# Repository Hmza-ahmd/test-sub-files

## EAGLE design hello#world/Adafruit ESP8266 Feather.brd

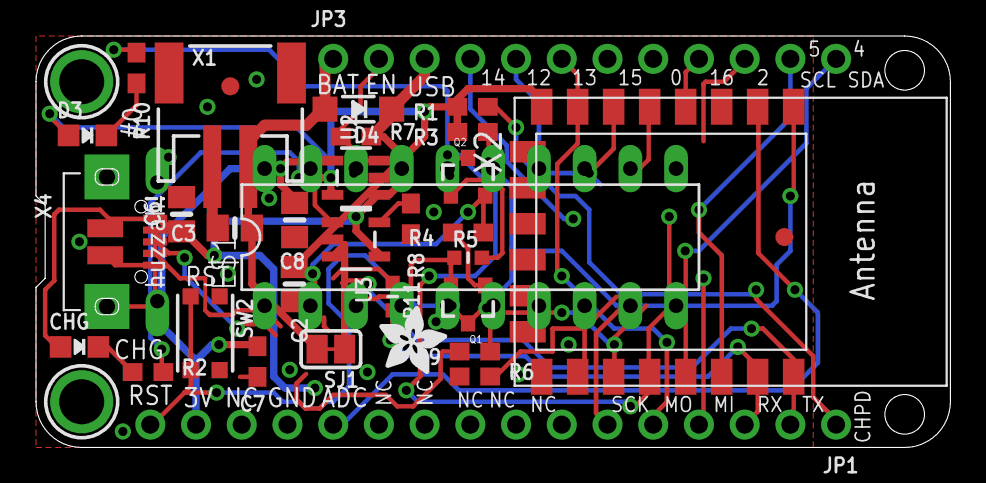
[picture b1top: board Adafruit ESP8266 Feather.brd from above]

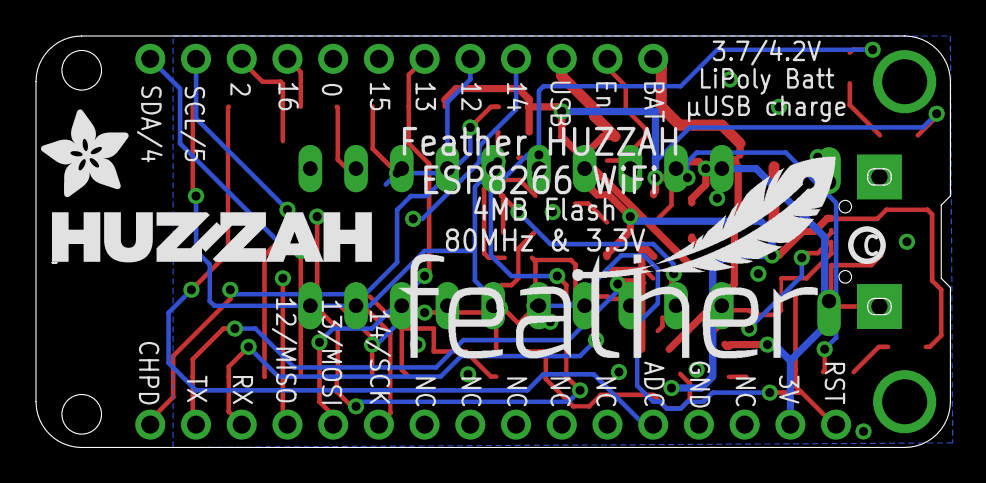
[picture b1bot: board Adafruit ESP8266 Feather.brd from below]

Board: 2 copper layers, 50.8 x 22.9 mm, 40 parts (4 on the bottom side), 27 nets.

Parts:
C2: 10uF; 0805-NO
C3, C6, C8: 10µF; 0805-NO
C7: 1uF; 0603-NO
CHG: ORANGE; CHIPLED_0805_NOOUTLINE
D3: RED; CHIPLED_0805_NOOUTLINE
D4: MBR120; SOD-123
E$1: DIL20
JP1: 1X16_ROUND
JP3: 1X12_ROUND
Q1, Q2: mmbt2222; SOT23-3
R1, R3, R4, R7, R9: 10K; 0603-NO
R2, R10: 1K; 0603-NO
R5: 10K; _0603MP
R6: 4.7K; 0603-NO
R8: 10K\; 0603-NO
R11: 1K; _0603MP
SJ1: SOLDERJUMPER_CLOSEDWIRE
SW2: KMR2; BTN_KMR2_4.6X2.8
U2: SPX3819; SOT23-5
U3: MCP73831T-2ACI/OT; SOT23-5
U$7: ADAFRUIT_5MM
U$9: FEATHERLOGO
U$13: PCBFEAT-REV-040
U$15: ADAFRUIT_3.5MM
U$23: HUZZAHLOGO
U$31, U$32: MOUNTINGHOLE2.5; MOUNTINGHOLE_2.5_PLATED
U$34, U$35: FIDUCIAL""; FIDUCIAL_1MM
X1: JSTPH; JSTPH2
X2: ESP-12; ESP-12E
X4: 20329; 4UCONN_20329_V2

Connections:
3.3V: C2.1, C7.1, C8.1, D3.A, JP1.15, R1.2, R3.2, R9.2, U2.5, X2.8
ADC: JP1.12, X2.2
CH_PD: JP1.1, R1.1
DTR: Q2.2, R4.1
EN: JP3.2, R7.1, U2.3
GND: C2.2, C3.2, C6.2, C7.2, C8.2, JP1.13, R6.1, R8.2, SW2.A, SW2.A', U2.2, U3.2, X1.1, X2.9, X4.BASE@1, X4.BASE@2, X4.GND, X4.SPRT@1, X4.SPRT@2, X4.SPRT@3, X4.SPRT@4
GPIO0: Q2.3, R10.1, X2.12
GPIO2: R9.1, X2.11
GPIO4/SDA: JP3.12, X2.13
GPIO5/SCL: JP3.11, X2.14
GPIO12/MISO: JP3.5, X2.6
GPIO13/MOSI: JP1.5, JP3.6, X2.7
GPIO15: R6.2, X2.10
GPIO16: JP3.9, X2.4
unnamed: CHG.C, R2.1
unnamed: R2.2, U3.1
unnamed: R8.1, U3.5
unnamed: D3.C, R10.2
unnamed: SJ1.1, U3.3
unnamed: Q1.1, R4.2
unnamed: Q2.1, R5.2
RESET: JP1.16, Q1.3, R3.1, SW2.B, SW2.B', X2.1
RTS: Q1.2, R5.1
RXD: JP1.3, R11.2, X2.15
TXD: JP1.2, X2.16
VBAT: C3.1, D4.A, JP3.1, SJ1.2, X1.2
VBUS: C6.1, CHG.A, D4.C, JP3.3, R7.2, U2.1, U3.4, X4.VBUS

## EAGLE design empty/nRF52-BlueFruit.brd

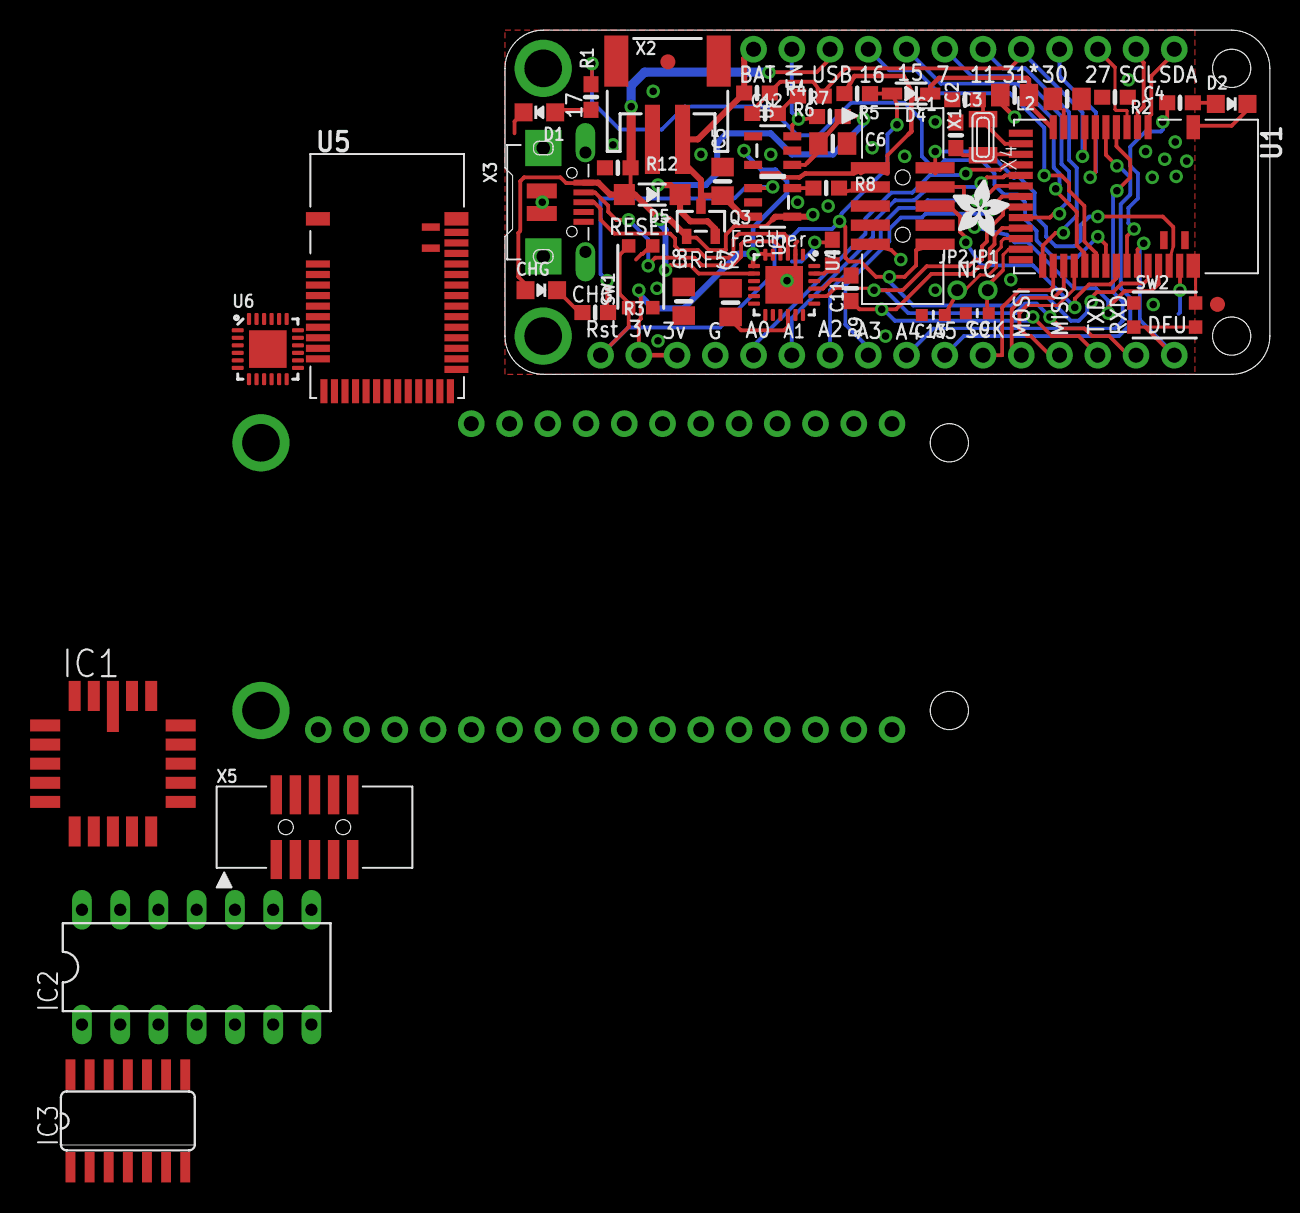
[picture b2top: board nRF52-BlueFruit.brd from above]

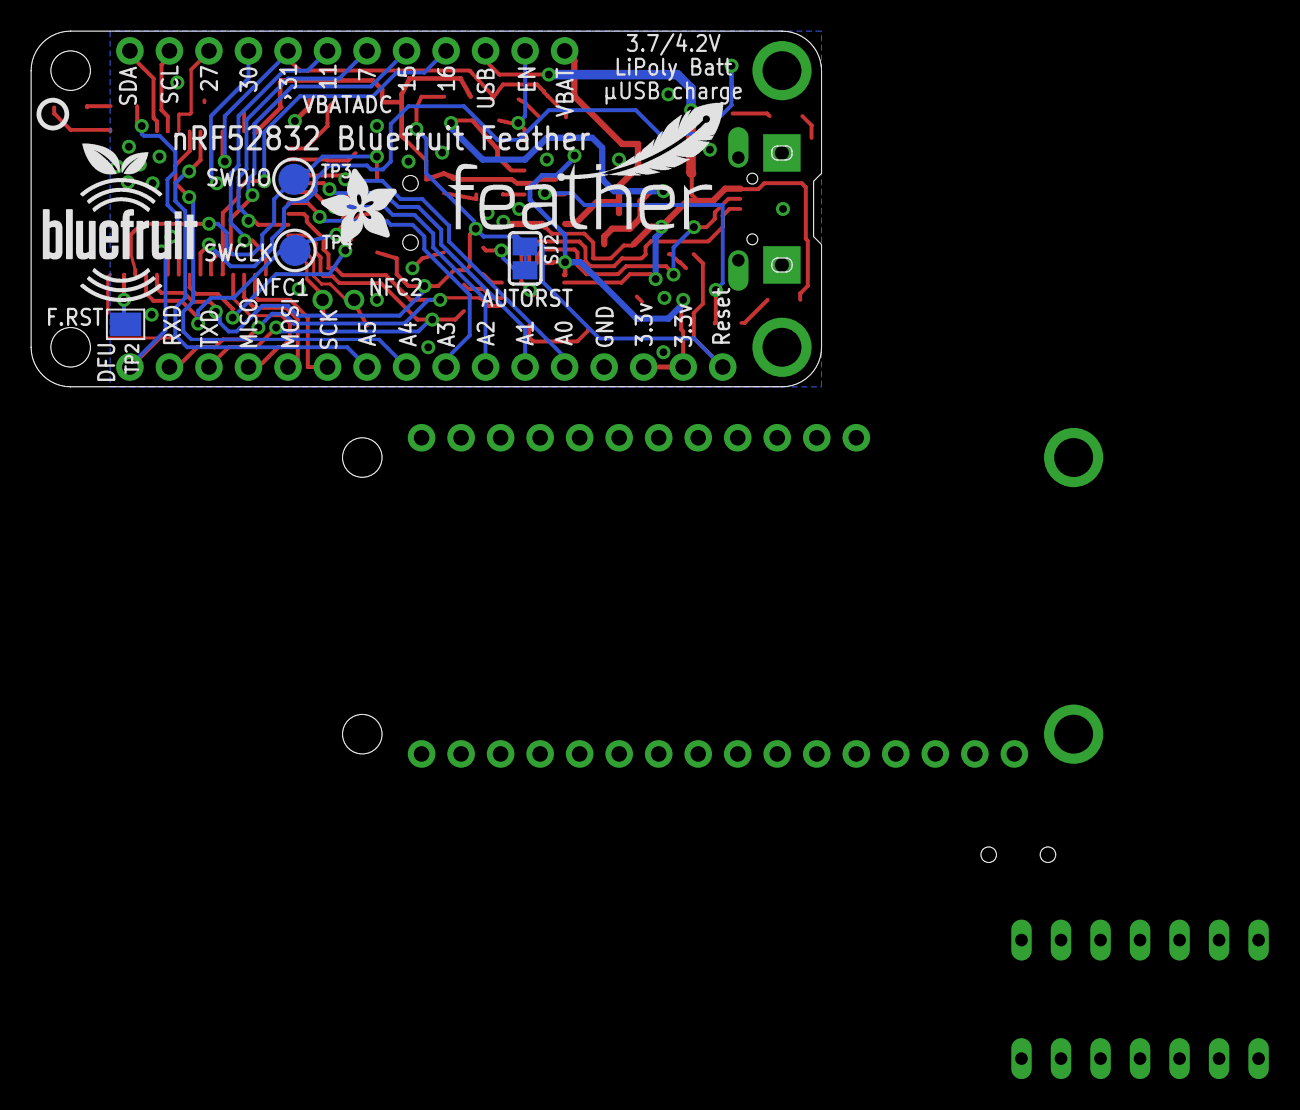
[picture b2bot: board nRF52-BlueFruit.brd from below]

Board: 2 copper layers, 50.8 x 22.9 mm, 60 parts (8 on the bottom side), 66 nets.

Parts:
C1, C2: 22pF; 0603-NO
C3: 10uF; 0805-NO
C4: 1uF; 0603-NO
C5, C6, C8: 10µF; 0805-NO
C7: 10uf; 0805-NO
C9, C13: 300pF; _0603MP
C11: 0.1uF; 0603-NO
C12: 1nF; 0603-NO
CHG: ORANGE; CHIPLED_0805_NOOUTLINE
D1: RED; CHIPLED_0805_NOOUTLINE
D2: BLUE; CHIPLED_0805_NOOUTLINE
D4: 1N4148; SOD-323
D5: MBR120; SOD-123
FID1, FID3: FIDUCIAL_1MM
IC1: 74ALS02FK; LCC20
IC2: 74S02N; DIL14
IC3: 7402D; SO14
JP1, JP2: 1X01_2MM
L2: 10uH; 0805-NO
MS1, MS2: FEATHERWING_NODIM
Q3: DMG3415U-7; SOT23-R
R1, R2, R3, R9: 1K; 0603-NO
R4: 806K; 0603-NO
R5: 100K; 0603-NO
R6: 2M; 0603-NO
R7, R8: 10K; 0603-NO
R12: 100k; 0603-NO
SJ2: BAT; SOLDERJUMPER_CLOSEDWIRE
SW1, SW2: KMR2; BTN_KMR2_4.6X2.8
TP2: FRST; PAD-1.5X2.0
TP3, TP4: TESTPOINT_ROUND_2MM
U1, U5: MDBT42; BLE_MODULE_RAYTAC_MDBT42
U2: AP2112(3.3V); SOT23-5
U3: MCP73831T-2ACI/OT; SOT23-5
U4, U6: CP2104; QFN24_4MM_SMSC
U$17: PCBFEAT-REV-040
U$45: BLUEFRUITLOGO_100MM
U$46: FEATHERLOGO_MED
U$47: ADAFRUIT_5MM
U$49: ADAFRUIT_3.5MM
X1, X5: 4u20317; 2X05_1.27MM_BOX_POSTS
X2: JSTPH; JSTPH2
X3: 4u20329; 4UCONN_20329_V2
X4: 32.768; XTAL3215

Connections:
3.3V: C3.1, D4.C, MS1.2, MS1.3, R7.2, U1.11, U4.5, U4.6, U4.7, U5.7, U6.5, X1.1
A0/0.02: MS1.5, U1.15, U5.15
A1/0.03: MS1.6, U1.16, U5.16
A2/0.04: MS1.7, U1.17, U5.17
A3/0.05: MS1.8, U1.18, U5.18
A4/0.28: MS1.9, U1.5
A5/0.29: MS1.10, U1.6, U5.2
A6/P0.30: MS1.20, MS2.20, U1.7, U5.3
A7/P0.31: C12.1, MS1.21, MS2.21, R4.2, R6.1, U1.8, U5.4
DFU: MS1.16, SW2.B, SW2.B', U1.34, U5.38
DTR: C11.2, U4.23, U6.1
EN: MS1.27, MS2.27, R5.1, U2.3
FRST: TP2.P$1, U1.38, U5.40
GND: C1.2, C2.2, C3.2, C4.2, C5.2, C6.2, C7.2, C8.2, C9.2, C12.2, C13.2, D1.C, D2.C, IC1.10, IC2.7, IC3.7, MS1.4, MS2.4, R6.2, R8.2, R12.1, SW1.B, SW1.B', SW2.A, SW2.A', U1.1, U1.12, U1.24, U1.39, U2.2, U3.2, U4.2, U4.THERM, U5.41, U6.2, X1.3, X1.5, X1.7, X1.9, X2.1, X3.BASE@1, X3.BASE@2, X3.GND, X3.SPRT@1, X3.SPRT@2, X3.SPRT@3, X3.SPRT@4, X5.3, X5.5
LED1: R1.2, U1.31, U5.35
LED2: R2.2, U1.33, U5.37
MISO: MS1.13, U1.28, U5.32
MOSI: MS1.12, U1.27, U5.31
unnamed: C1.1, U1.13, U5.13, X4.P$1
unnamed: C2.1, U1.14, U5.14, X4.P$2
unnamed: U1.10, U5.6
unnamed: CHG.C, R3.1
unnamed: D1.A, R1.1
unnamed: U4.15, U6.9
unnamed: D2.A, R2.1
unnamed: R3.2, U3.1
unnamed: R8.1, U3.5
unnamed: R9.1, U4.21, U6.23
unnamed: U4.1, U6.11
unnamed: C11.1, SJ2.2
unnamed: C7.1, U4.16, U6.4
unnamed: U4.22, U6.24
unnamed: U4.19, U6.21
unnamed: U4.18, U6.20
unnamed: U4.14, U6.17
unnamed: U4.12, U6.14
unnamed: U4.11, U6.13
unnamed: U1.9, U5.5
unnamed: IC1.3, IC2.1
unnamed: IC1.9, IC1.12
unnamed: IC1.6, IC1.13
unnamed: IC1.2, IC2.2
OUT: C8.1, U2.5
P0.07: MS1.23, MS2.23, U1.20, U5.20
P0.09/NFC1: C13.1, JP2.1, U1.22, U5.22
P0.10/NFC2: C9.1, JP1.1, U1.23, U5.23
P0.11: MS1.22, MS2.22, U1.25, U5.29
P0.15: MS1.24, MS2.24, U1.29, U5.33
P0.16: MS1.25, MS2.25, U1.30, U5.34
P0.27: MS1.19, MS2.19, U1.4
RESET: D4.A, MS1.1, R7.1, SJ2.1, SW1.A, SW1.A', U1.35, U5.39, X1.10
RXD: MS1.14, R9.2, U1.21, U5.21
SCK: MS1.11, U1.26, U5.30
SCL: MS1.18, MS2.18, U1.3
SDA: MS1.17, MS2.17, U1.2, U5.1
SWCLK: TP4.P$1, U1.36, X1.4
SWDIO: TP3.P$1, U1.37, X1.2
SWO: U1.32, U5.36, X1.6
TXD: MS1.15, U1.19, U4.20, U5.19, U6.22
USB: MS1.26, MS2.26
USBD+: U4.3, X3.D+
USBD-: U4.4, U6.8, X3.D-
VBAT: C5.1, MS1.28, MS2.28, Q3.3, R4.1, U3.3, X2.2
VBUS: CHG.A, D5.A, Q3.1, R12.2, U3.4, U4.8, X3.VBUS
VCC: IC1.20, IC2.14, IC3.14, X5.1
VIN: C6.1, D5.C, Q3.2, R5.2, U2.1

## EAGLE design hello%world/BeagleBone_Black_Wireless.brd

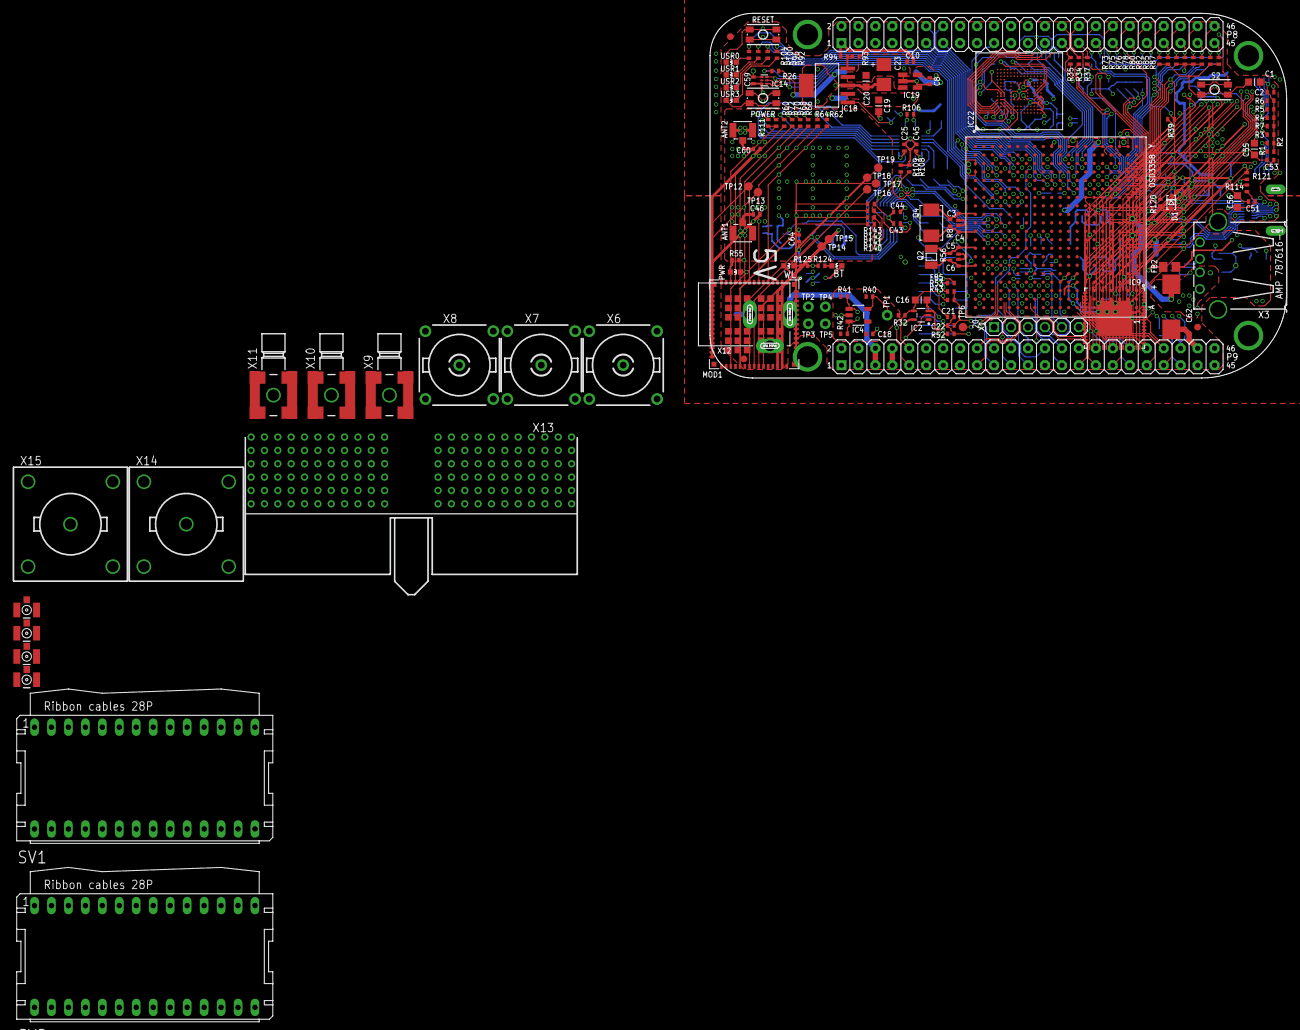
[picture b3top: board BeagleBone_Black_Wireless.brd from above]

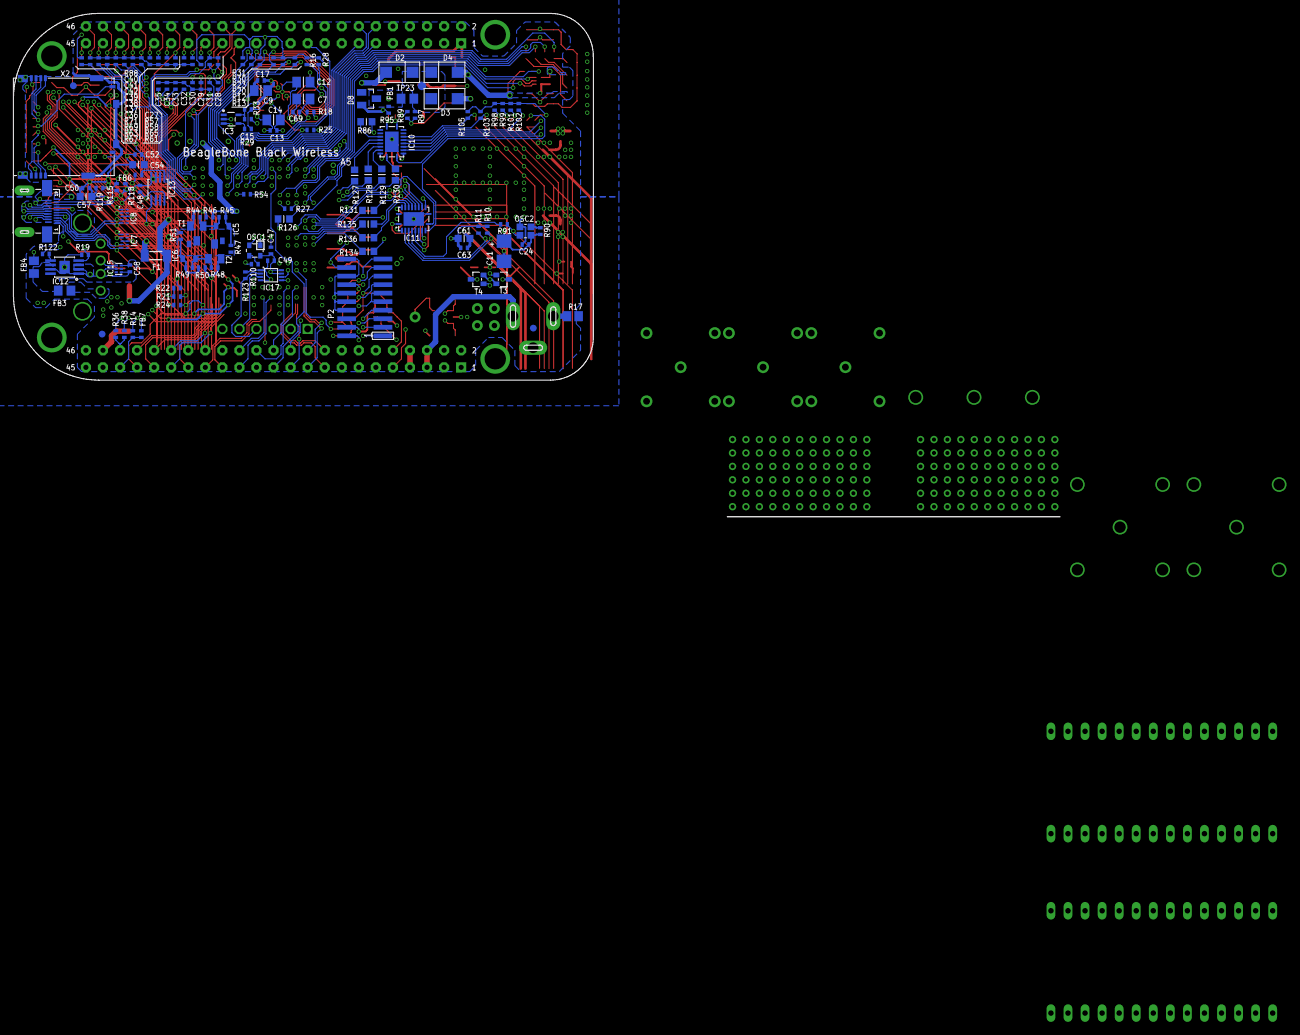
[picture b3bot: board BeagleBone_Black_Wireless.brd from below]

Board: 6 copper layers, 86.4 x 54.6 mm, 289 parts (138 on the bottom side), 177 nets.

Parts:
ANT1, ANT2: U.FL-R-SMT-1(10); U.FL-R-SMT-1
BT: LTST-C191TBKT; 0603-LED
C1: 10uF,10V; C0603K
C2, C13, C15, C17, C18, C21, C22, C24, C25, C43, C44, C45, C47, C48, C49, C50, C51, C52, C53, C58, C59, C63, C69: .1uF, 6.3V; C0402K
C3, C4, C5, C6: 18pF, 50V; C0402K
C7: 4.7uF, 6.3V; C0805K
C8, C10: 1uF; C0402K
C9, C12, C14: 2.2uF, 6.3V; C0805K
C11, C23: 47uF DNP; CT3528
C16, C54, C55, C56, C57: 2.2uF, 6.3V; C0603K
C19, C20, C61: 10uF, 6.3V; C0603K
C27, C28, C29, C30, C31, C32, C33, C34, C35, C36, C37, C38, C39, C40, C41, C42: 47pF, 6.3V; C0402K
C46, C60: 10pF; C0402K
C62: 220uF 6.3V; D/7343-31W
C64: 1uF, 6.3V; C0402K
D1: RB751V40,115; SOD323(NXP)REFLOW
D2: STPS140A DNP; DIODE_SMA
D3, D4: STPS140A; DIODE_SMA
D8: BAT54C; SOT23
F1: 1206L025YR; SM-1206
FB1: 220 Ohm 800mA; 0805-RESISTOR
FB2: 2.5k Ohm (BLM18BD252SN1D); 0805-RESISTOR
FB3: 150 Ohm 800mA; 0805-RESISTOR
FB4: 0.1 Ohm, 0805; 0805-RESISTOR
FB5, FB6, FB7: 1k BLM15AG102SN1D; R0402
FUD1, FUD2, FUD3, FUD4, FUD5, FUD6: FIDUCIAL; FIDUCIAL_40MIL
IC1: OSD3358
IC2: SN74LVC1G07DCK; SC70(TI-DCK)
IC3: SN74LVC1G06DCK; SC70(TI-DCK)
IC4: 24LC32AT-I/OT; SOT23-5(MICROCHIP)
IC5: TLVH431 (SOT-23-3); DBZ_R-PDSO-G3
IC6: DNP TLVH431 (SOT-23-3); DBZ_R-PDSO-G3
IC7, IC8: IP4283CZ10-TBR; SOT1176-1(NXP)
IC9: TDA19988BHN/C1,557; SOT804-4(NXP)
IC10, IC11: TXS0108ERGYR; R-PVQFN-N20(TI)
IC12: TPS2051BDGN; MSOP-POWER.PAD-8(TI)
IC13: SN74AUC1G74; SM8-8(TI)
IC14, IC15: TPD4S012DRY; SON-6(TI)-DRY
IC17: SN74LVC2G241DCUR; VSSOP8(TI)
IC18: TL1963ADCQR; SOT-223(DCQ_R-PDSO-G6_TI)
IC19: AP2112K-1.8TRG1 3.3V; SOT23-5
IC22: MICRON_EMMC_153
MGT1, MGT2, MGT3, MGT4: MOUNTING_HOLE
MOD1: WL1835MODGBMOCT; MOC-100(TI)
OSC1: ASDMB-24.576MHZ-LC-T; OSCILLATOR-2.5X2.0-BBB
OSC2: NZ2520SB-32.768KHZ-NSA3534C; NZ2520S
P2: JTAG
P8, P9: TH-2X23
POWER: MINI_PUSHBUTTON
PWR: LTST-C191TBKT; 0603-LED
Q2: 32.768kHz; CRYSTAL_3.2X1.5
Q4: 24 MHz; CRYSTAL_5X3.2MM
R1, R2, R3, R4, R5, R6, R7, R12, R13, R16, R18, R19, R20, R23, R24, R25, R28, R30, R31, R32, R33, R40, R119, R121: 10k, 1%; R0402
R8: 1M, 1%; R0402
R10, R11: 150k; R0402
R14, R26, R27, R29, R35, R36, R37, R38, R39, R54, R114, R122: 0, 1%; R0402
R17: .1, 0805; R0805
R21, R22, R43, R52, R53, R55: 4.75k, 1%; R0402
R34: 22; R0402
R41, R42, R115, R118: 1.5k, 1%; R0402
R44: 499; R0402
R45, R49: DNP; R0402
R46: 10k 1%; R0402
R47: 40.2k 1%; R0402
R48: DNP 499; R0402
R50: DNP 10k 1%; R0402
R51: DNP 40.2k 1%; R0402
R56: DNP 1M, 1%; R0402
R57, R58, R61, R63, R65, R67, R69, R71, R73, R75, R76, R78, R80, R82, R85, R87, R123: 100k, 1%; R0402
R60, R62, R64, R66, R68, R70, R72, R140, R141, R142, R143: 33, 5%; R0402
R86, R126, R127, R128, R129, R130, R131, R134, R135, R136: 33, 5%; R0603
R88: 100, 1%; R0402
R89, R90, R92, R96, R100, R104, R124, R125: 1k; R0402
R91: 0 DNP; R0402
R93: 7.15k; R0402
R94: 4.12k; R0402
R95: 1M; R0402
R97, R108, R109: DNP 1k; R0402
R98, R99, R101, R102, R103, R105: 10k; R0402
R106: 1.5k; R0402
R110: 33; R0402
R111: DNP 10k; R0402
R120: 27k, 1%; R0402
RESET: MINI_PUSHBUTTON
S2: MINI_PUSHBUTTON
SV1, SV2: 28PL
T1: MMBT2907; SOT23-BEC
T2: DNP MMBT2907; SOT23-BEC
T3, T4: BSS138W-7-F; SOT-323(DIODES)
TP1, TP2, TP3, TP4, TP5: TESTPAD/W_HOLE_1X1
TP6, TP12, TP13, TP14, TP15, TP16, TP17, TP18, TP19, TP23: PTR1B1,27; B1,27
USR0, USR1, USR2, USR3: LTST-C191TBKT; 0603-LED
WL: LTST-C191TBKT; 0603-LED
X1: TH-1X6
X2: SCHA5B0200
X3: USB_HOST_HORIZONTAL_W/CHASSIS_GND
X5: 10118241-001RLF; HDMI-TYPE-D-10118241
X6, X7, X8: A1944-50; A1944
X9, X10, X11: PE44121
X12: PJ-102B_POWER_CON
X13: 1620-110
X14, X15: B35N57
X16, X17, X18, X19: MC-921

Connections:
1.8V-WIFI: C8.1, C11.+, C24.1, C25.1, C43.1, C64.1, IC10.2, IC11.2, IC19.5, MOD1.38, OSC2.4, R90.1, R98.1, R99.1, R101.1, R102.1, R103.1, R105.1, R111.1
3.3V-WIFI: C10.1, C20.1, C23.+, C44.1, C45.1, C61.1, C63.1, IC10.19, IC11.19, IC18.4, IC19.1, IC19.3, MOD1.46, MOD1.47, R93.1, R124.2, R125.2
5V_IN: C19.1, D8.3, FB1.2, IC18.2, R95.1
12MHZ: FB6.2, IC9.27
12M_LOOP: IC13.2, IC13.3
32.768KHZ: MOD1.36, OSC2.3, R91.2
AGND: IC1.E8, P9.34
AIN7: IC12.5, R21.2, R22.1, R122.2
ALT.BT.EN: IC11.17, R135.2
ALT.BUFF.OE: IC10.10, IC11.10, R106.1, R131.1
ALT.WL.CLK: IC10.15, R126.2
ALT.WL.CMD: IC10.14, R86.2
ALT.WL.D0: IC10.20, R130.2
ALT.WL.D1: IC10.18, R129.2
ALT.WL.D2: IC10.17, R128.2
ALT.WL.D3: IC10.16, R127.2
ALT.WL.EN: IC11.18, R136.2
ALT.WL.IRQ: IC11.12, R134.2
BT_EN: IC11.4, MOD1.41, R11.1, T4.G
BT_HCI_CTS: IC11.8, R141.2
BT_HCI_CTS.SIP: IC11.15, R108.1
BT_HCI_RTS: IC11.6, R140.2
BT_HCI_RTS.SIP: IC11.13, R109.1
BT_HCI_RX: IC11.1, R143.2
BT_HCI_TX: IC11.7, R142.2
CEC: D1.C, IC9.30, X5.15
CGND: MGT1.P$1, MGT2.P$1, MGT3.P$1, MGT4.P$1, R17.2, X2.CGND1, X2.CGND2, X2.CGND3, X2.CGND4, X2.CGND5, X2.CGND6, X3.5, X3.6, X5.CG1, X5.CG2, X5.CG3, X5.CG4
CLKOUT2: FB7.1, IC11.16, P2.18, P9.41, R14.1
DVI_5V: F1.1, R115.1, R118.1, X5.19
EMMC_RSTN: IC22.K5, R29.1, R33.1
EXT_SWING: IC9.34, R119.1
GND: ANT1.GND1, ANT1.GND2, ANT2.GND1, ANT2.GND2, C1.2, C2.2, C7.2, C8.2, C9.2, C10.2, C11.-, C12.2, C13.2, C14.2, C15.2, C16.2, C17.2, C18.2, C19.2, C20.2, C21.2, C22.2, C23.-, C24.2, C25.2, C27.2, C28.2, C29.2, C30.2, C31.2, C32.2, C33.2, C34.2, C35.2, C36.2, C37.2, C38.2, C39.2, C40.2, C41.2, C42.2, C43.2, C44.2, C45.2, C47.2, C48.2, C49.2, C50.2, C51.2, C52.2, C53.2, C54.2, C55.2, C56.2, C57.2, C58.2, C59.2, C61.2, C62.-, C63.2, C64.2, C69.2, D8.2, IC1.A1, IC1.A18, IC1.E19, IC1.E20, IC1.F8, IC1.F19, IC1.G8, IC1.G9, IC1.G11, IC1.G12, IC1.G19, IC1.H6, IC1.H7, IC1.H8, IC1.H9, IC1.H10, IC1.H12, IC1.H19, IC1.J6, IC1.J7, IC1.J8, IC1.J9, IC1.J10, IC1.J11, IC1.J19, IC1.J20, IC1.K7, IC1.K9, IC1.K10, IC1.K11, IC1.K19, IC1.L10, IC1.L11, IC1.L12, IC1.L13, IC1.L19, IC1.M6, IC1.M7, IC1.M8, IC1.M9, IC1.M10, IC1.M12, IC1.M14, IC1.M19, IC1.N7, IC1.N10, IC1.N11, IC1.N14, IC1.N19, IC1.N20, IC1.P19, IC1.P20, IC1.R19, IC1.R20, IC1.T19, IC1.T20, IC1.U19, IC1.V1, IC1.V18, IC1.V19, IC1.W2, IC1.W3, IC1.W5, IC1.W6, IC1.W7, IC1.W8, IC1.W9, IC1.W10, IC1.W11, IC1.W12, IC1.W13, IC1.W14, IC1.W15, IC1.W16, IC1.W17, IC1.W18, IC1.W19, IC1.W20, IC1.Y7, IC1.Y10, IC1.Y12, IC1.Y15, IC1.Y18, IC2.3, IC3.3, IC4.2, IC7.3, IC7.8, IC8.3, IC8.8, IC9.8, IC9.9, IC9.16, IC9.17, IC9.18, IC9.19, IC9.53, IC9.54, IC9.61, IC9.62, IC9.63, IC9.65, IC10.11, IC10.TP, IC11.11, IC11.TP, IC12.1, IC12.9, IC13.4, IC14.4, IC15.4, IC17.1, IC17.4, IC18.3, IC18.6, IC19.2, IC22.C4, IC22.E7, IC22.G5, IC22.H10, IC22.K8, IC22.N2, IC22.N5, IC22.P4, IC22.P6, MOD1.1, MOD1.7, MOD1.9, MOD1.15, MOD1.16, MOD1.17, MOD1.19, MOD1.20, MOD1.23, MOD1.24, MOD1.28, MOD1.29, MOD1.30, MOD1.31, MOD1.33, MOD1.34, MOD1.35, MOD1.37, MOD1.39, MOD1.44, MOD1.45, MOD1.48, MOD1.49, MOD1.54, MOD1.55, MOD1.59, MOD1.61, MOD1.63, MOD1.64, MOD1.G1, MOD1.G2, MOD1.G3, MOD1.G4, MOD1.G5, MOD1.G6, MOD1.G7, MOD1.G8, MOD1.G9, MOD1.G10, MOD1.G11, MOD1.G12, MOD1.G13, MOD1.G14, MOD1.G15, MOD1.G16, MOD1.G17, MOD1.G18, MOD1.G19, MOD1.G20, MOD1.G21, MOD1.G22, MOD1.G23, MOD1.G24, MOD1.G25, MOD1.G26, MOD1.G27, MOD1.G28, MOD1.G29, MOD1.G30, MOD1.G31, MOD1.G32, MOD1.G33, MOD1.G34, MOD1.G35, MOD1.G36, OSC1.2, OSC2.2, P2.4, P2.8, P2.10, P2.12, P2.16, P2.20, P8.1, P8.2, P9.1, P9.2, P9.43, P9.44, P9.45, P9.46, POWER.1, POWER.2, R10.2, R11.2, R17.1, R19.2, R22.2, R24.1, R27.2, R52.2, R55.1, R57.1, R61.1, R63.1, R65.1, R67.1, R69.1, R71.1, R73.1, R75.1, R85.1, R87.1, R94.2, R95.2, R106.2, R108.2, R109.2, R114.1, R119.2, R123.2, RESET.1, RESET.2, S2.3, S2.4, T3.S, T4.S, TP5.P$1, USR0.K, USR1.K, USR2.K, USR3.K, X1.1, X2.6, X2.GND, X3.4, X5.4, X5.7, X5.10, X5.13, X5.16, X12.OUT
GPIO0_7: P9.42, R36.1, R38.1
GPIO1_16: P9.15, R54.1
GPIO3_21: P9.25, R110.2
HDMI.DSCL: IC9.33, R115.2, X5.17
HDMI.DSDA: IC9.32, R118.2, X5.18
HDMI_1V8: C50.1, C51.1, C52.1, C53.1, C54.1, C55.1, C56.1, C57.1, FB2.2, IC9.5, IC9.14, IC9.29, IC9.35, IC9.36, IC9.41, IC9.46, IC9.47, IC9.48, IC9.55
HDMI_INT: IC9.50, R121.2
HPD: IC9.31, X5.1
I2C0_SCL: IC4.1, IC9.52, R41.2
I2C0_SDA: IC4.3, IC9.51, R42.2
JTAG_EMU0: P2.13, R43.2
JTAG_EMU1: P2.14, R53.2
JTAG_TCK: P2.9, P2.11
JTAG_TRSTN: P2.2, R52.1
LCD.CLOCK: IC9.4, P8.28, R34.1
LCD.D0.B0--B3: C42.1, IC9.15, P8.45, R87.2
LCD.D1.B1--B4: C41.1, IC9.13, P8.46, R85.2
LCD.D2.B2--B5: C40.1, IC9.12, P8.43, R82.1, R88.1
LCD.D3.B3--B6: C39.1, IC9.11, P8.44, R80.1
LCD.D4.B4--B7: C38.1, IC9.10, P8.41, R78.1
LCD.D5.G0--G2: C37.1, IC9.7, P8.42, R76.1
LCD.D6.G1--G3: C36.1, IC9.6, P8.39, R75.2
LCD.D7.G2--G4: C35.1, IC9.3, P8.40, R73.2
LCD.D8.G3--G5: C34.1, IC9.2, P8.37, R71.2
LCD.D9.G4--G6: C33.1, IC9.1, P8.38, R69.2
LCD.D10.G5--G7: C32.1, IC9.64, P8.36, R67.2
LCD.D11.R0--R3: C31.1, IC9.60, P8.34, R65.2
LCD.D12.R1--R4: C30.1, IC9.59, P8.35, R63.2
LCD.D13.R2--R5: C29.1, IC9.58, P8.33, R61.2
LCD.D14.R3--R6: C28.1, IC9.57, P8.31, R58.1
LCD.D15.R4--R7: C27.1, IC9.56, P8.32, R57.2
LCD.ENABLE: IC9.20, P8.30, R39.1
LCD.HSYNC: IC9.22, P8.29, R37.1
LCD.VSYNC: IC9.21, P8.27, R35.1
MMC1_CLK: IC22.M6, P8.21, R31.1
MMC1_CMD: IC22.M5, P8.20, R30.1
MMC1_DAT0: IC22.A3, P8.25, R12.1
MMC1_DAT1: IC22.A4, P8.24, R13.1
MMC1_DAT2: IC22.A5, P8.5, R16.1
MMC1_DAT3: IC22.B2, P8.6, R18.1
MMC1_DAT4: IC22.B3, P8.23, R20.1
MMC1_DAT5: IC22.B4, P8.22, R23.1
MMC1_DAT6: IC22.B5, P8.3, R25.1
MMC1_DAT7: IC22.B6, P8.4, R28.1
unnamed: OSC2.1, R90.2
unnamed: R88.2, S2.1, S2.2
unnamed: PWR.K, R55.2
unnamed: IC18.1, R89.2, R97.2
unnamed: C4.1, Q4.1, R8.1
unnamed: C3.1, Q4.2, R8.2
unnamed: IC18.5, R93.2, R94.1
unnamed: C3.2, C4.2
unnamed: C5.2, C6.2
unnamed: ANT2.SIG, C60.1
unnamed: ANT1.SIG, C46.1
unnamed: C46.2, MOD1.32
unnamed: R100.1, USR1.A
unnamed: R96.1, USR2.A
unnamed: R92.1, USR3.A
unnamed: C60.2, MOD1.18
unnamed: IC1.B4, R24.2
unnamed: X16.2@1, X16.2@2
unnamed: T3.D, WL.K
unnamed: X14.2, X14.3, X14.4, X14.5, X15.1, X15.2, X15.3, X15.4, X15.5
unnamed: IC3.4, R29.2
unnamed: MOD1.26, TP12.TP
unnamed: R104.1, USR0.A
unnamed: MOD1.27, TP13.TP
unnamed: C5.1, Q2.P$1, R56.2
unnamed: C6.1, Q2.P$2, R56.1
unnamed: MOD1.42, TP14.TP
unnamed: MOD1.43, TP15.TP
unnamed: MOD1.56, TP16.TP
unnamed: MOD1.57, TP17.TP
unnamed: OSC1.3, R110.1
unnamed: MOD1.58, TP18.TP
unnamed: MOD1.60, TP19.TP
unnamed: C7.1, C69.1, IC22.C2
unnamed: IC5.2, R44.2, R45.1, T1.B
unnamed: IC5.1, R45.2, R46.2, R47.1
unnamed: IC6.2, R48.2, R49.1, T2.B
unnamed: IC6.1, R49.2, R50.2, R51.1
unnamed: IC4.5, R40.2, TP1.P$1
unnamed: BT.K, T4.D
unnamed: R125.1, WL.A
unnamed: FB6.1, IC13.5
unnamed: BT.A, R124.1
unnamed: MOD1.14, R60.1, R111.2
unnamed: MOD1.13, R72.1
unnamed: MOD1.12, R70.1
unnamed: MOD1.11, R68.1
unnamed: D1.A, R120.2
unnamed: MOD1.10, R66.1
unnamed: MOD1.8, R64.1
unnamed: MOD1.6, R62.1
unnamed: MOD1.50, R140.1
unnamed: MOD1.51, R141.1
unnamed: MOD1.52, R142.1
unnamed: MOD1.53, R143.1
PWR_BUT: P9.9, POWER.3, POWER.4
RX<-TX: IC17.3, X1.5
SD.CD: P2.19, R7.1, X2.CD
SD.CLK: R3.1, X2.5
SD.CMD: R4.1, X2.3
SD.D0: R2.1, X2.7
SD.D1: R1.1, X2.8
SD.D2: R6.1, X2.1
SD.D3: R5.1, X2.2
SELECT_5V: D2.K, D3.K, D4.K, FB1.1, R97.1, TP23.TP
SLOW_CLK: IC11.5, R91.1
SPI1_CS0: IC9.25, P9.28
SPI1_D0: IC9.24, P9.29
SPI1_SCLK: IC9.23, P9.31
SYS_5V: C62.+, D2.A, F1.2, IC12.2, IC12.3, P9.7, P9.8
SYS_RESET#: C16.1, C21.1, IC2.4, P2.15, P9.10, R32.2, RESET.3, RESET.4
TEST: IC9.49, R114.2
TX0+: IC8.5, IC9.40, X5.9
TX0-: IC8.4, IC9.39, X5.11
TX1+: IC7.2, IC9.43, X5.6
TX1-: IC7.1, IC9.42, X5.8
TX2+: IC7.5, IC9.45, X5.3
TX2-: IC7.4, IC9.44, X5.5
TX->RX: IC17.2, R123.1, X1.4
TXC+: IC8.2, IC9.38, X5.12
TXC-: IC8.1, IC9.37, X5.14
USB1_DRVVBUS: IC12.4, R19.1
USB.HOST.D+: IC15.1, X3.3
USB.HOST.D-: IC15.2, X3.2
USB_DC: C59.1, D4.A, IC14.6, R26.2
VBUS.HOST: FB3.2, X3.1
VBUS.OUT: C58.1, FB3.1, FB4.1, IC12.6, IC12.7, IC12.8, IC15.6
VDD_1V8: FB2.1, IC1.D10, IC1.E9, IC2.5, IC5.3, IC6.3, R47.2, R51.2, T1.C, T2.C
VDD_3V3A: IC1.N5, IC1.P5, IC1.P6, IC1.P7, R44.1, R46.1, T1.E
VDD_3V3B: C1.1, C2.1, C9.1, C12.1, C13.1, C14.1, C15.1, C17.1, C18.1, C22.1, C47.1, C48.1, C49.1, IC3.5, IC4.4, IC13.6, IC13.7, IC13.8, IC17.7, IC17.8, IC22.C6, IC22.E6, IC22.F5, IC22.J10, IC22.K9, IC22.M4, IC22.N4, IC22.P3, IC22.P5, OSC1.4, P2.5, P9.3, P9.4, R1.2, R2.2, R3.2, R4.2, R5.2, R6.2, R7.2, R12.2, R13.2, R16.2, R18.2, R20.2, R21.1, R23.2, R25.2, R28.2, R30.2, R31.2, R32.1, R33.2, R40.1, R41.1, R42.1, R43.1, R48.1, R50.1, R53.1, R58.2, R76.2, R78.2, R80.2, R82.2, R89.1, R120.1, R121.1, R122.1, T2.E, X2.4
VDD_5V: D3.A, P9.5, P9.6, X12.IN
VDD_ADC: IC1.D8, P9.32
WL_EN: IC11.3, MOD1.40, R10.1, T3.G
WL_IRQ: IC11.9, R60.2
WL_SDIO_CLK: IC10.6, R64.2, R103.2
WL_SDIO_CMD: IC10.7, R62.2, R105.2
WL_SDIO_D0: IC10.1, R66.2, R98.2
WL_SDIO_D1: IC10.3, R68.2, R99.2
WL_SDIO_D2: IC10.4, R70.2, R101.2
WL_SDIO_D3: IC10.5, R72.2, R102.2
XDMA_EVENT_INTRO: FB5.2, IC13.1, P2.17

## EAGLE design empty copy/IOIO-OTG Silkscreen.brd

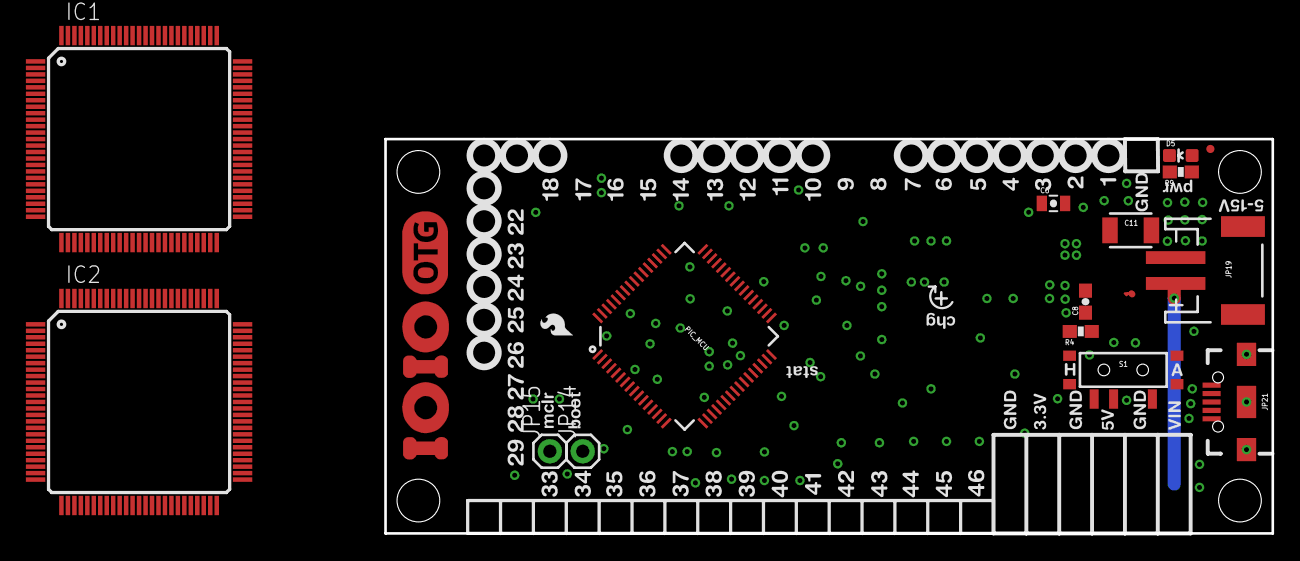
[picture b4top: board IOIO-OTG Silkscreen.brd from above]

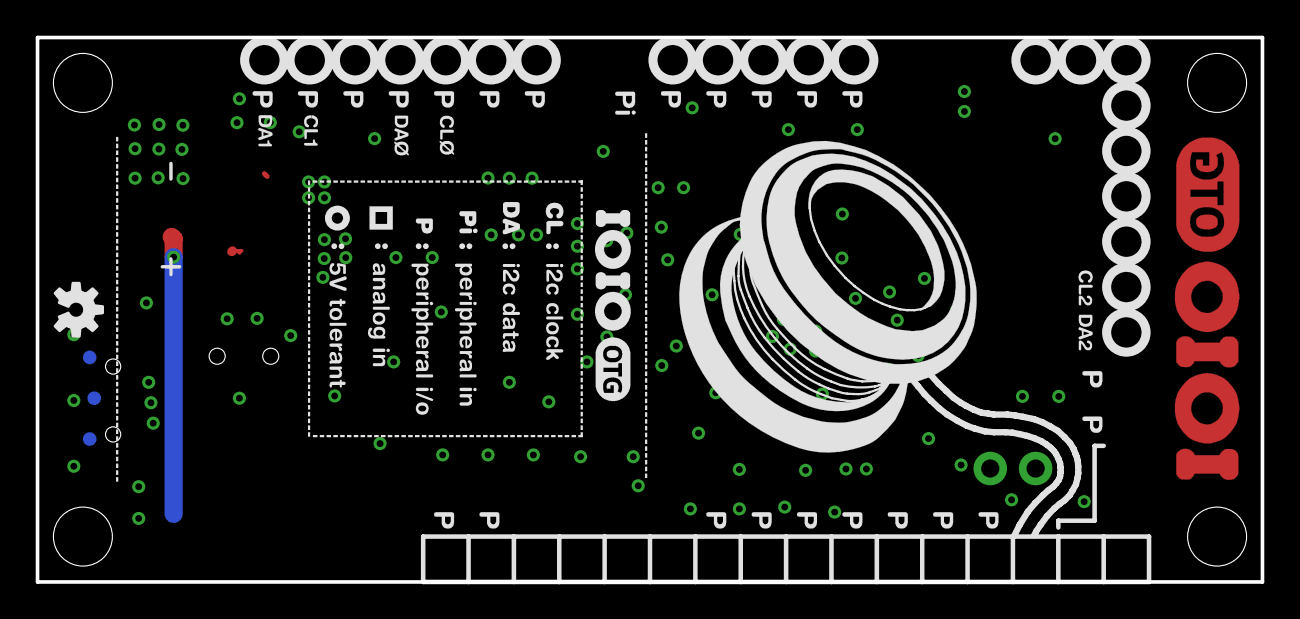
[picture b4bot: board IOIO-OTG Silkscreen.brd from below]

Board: 2 copper layers, 68.6 x 30.5 mm, 26 parts (4 on the bottom side), 3 nets.

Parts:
C6: 10uF; 0805-CAP
C8: 3.3nF; 0603-CAP
C11: 10uF; 1210
D5: Red; LED-0603
FRAME2: FRAME-LEDGER; CREATIVE_COMMONS
IC1, IC2: TQFP100
JP10, JP11, JP12, JP13: STAND-OFF
JP14, JP15: 1X01
JP16: FIDUCIALUFIDUCIAL; MICRO-FIDUCIAL
JP19: JST; JST-2-SMD
JP21: AB MICRO USB; USB-AB-MICRO-SMD_V03
LOGO1: OSHW-LOGOS; OSHW-LOGO-S
LOGO3: SFE_LOGO_FLAME.1_INCH; SFE_LOGO_FLAME_.1
PIC_MCU: PIC24FJ256GB206; PIC24FXXX_TQFP64
R4: 3.3k; 0603-RES
R9: 1.6K; 0603-RES
S1: SWITCH_SPDT; KPS-1290
TP1, TP2, TP3: TEST-POINT3; PAD.03X.03
U$6: IOIO-OTG; IOIO-OTG-COPPER-EXPOSED

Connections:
ANCHOR1: JP21.SHIELD1, JP21.SHIELD2, JP21.SHIELD3
GND: IC1.13, IC1.26, IC1.39, IC1.50, IC1.63, IC1.76, IC1.89, IC1.100, IC2.13, IC2.26, IC2.39, IC2.50, IC2.63, IC2.76, IC2.89, IC2.100
VCC: IC1.12, IC1.40, IC1.62, IC1.90, IC2.12, IC2.40, IC2.62, IC2.90

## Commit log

2021-01-14 1st commit

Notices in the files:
parts and their libraries:
SparkFun-Passives: Licensing: CC v3.0 Share-Alike You are welcome to use this library for commercial purposes.
SparkFun-Aesthetics: Released under the Creative Commons Attribution Share-Alike 4.0 License
SparkFun-Aesthetics: https://creativecommons.org/licenses/by-sa/4.0
